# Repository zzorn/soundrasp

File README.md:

soundrasp
=========

Modular sound synthetizator, with designs for a physical controller.

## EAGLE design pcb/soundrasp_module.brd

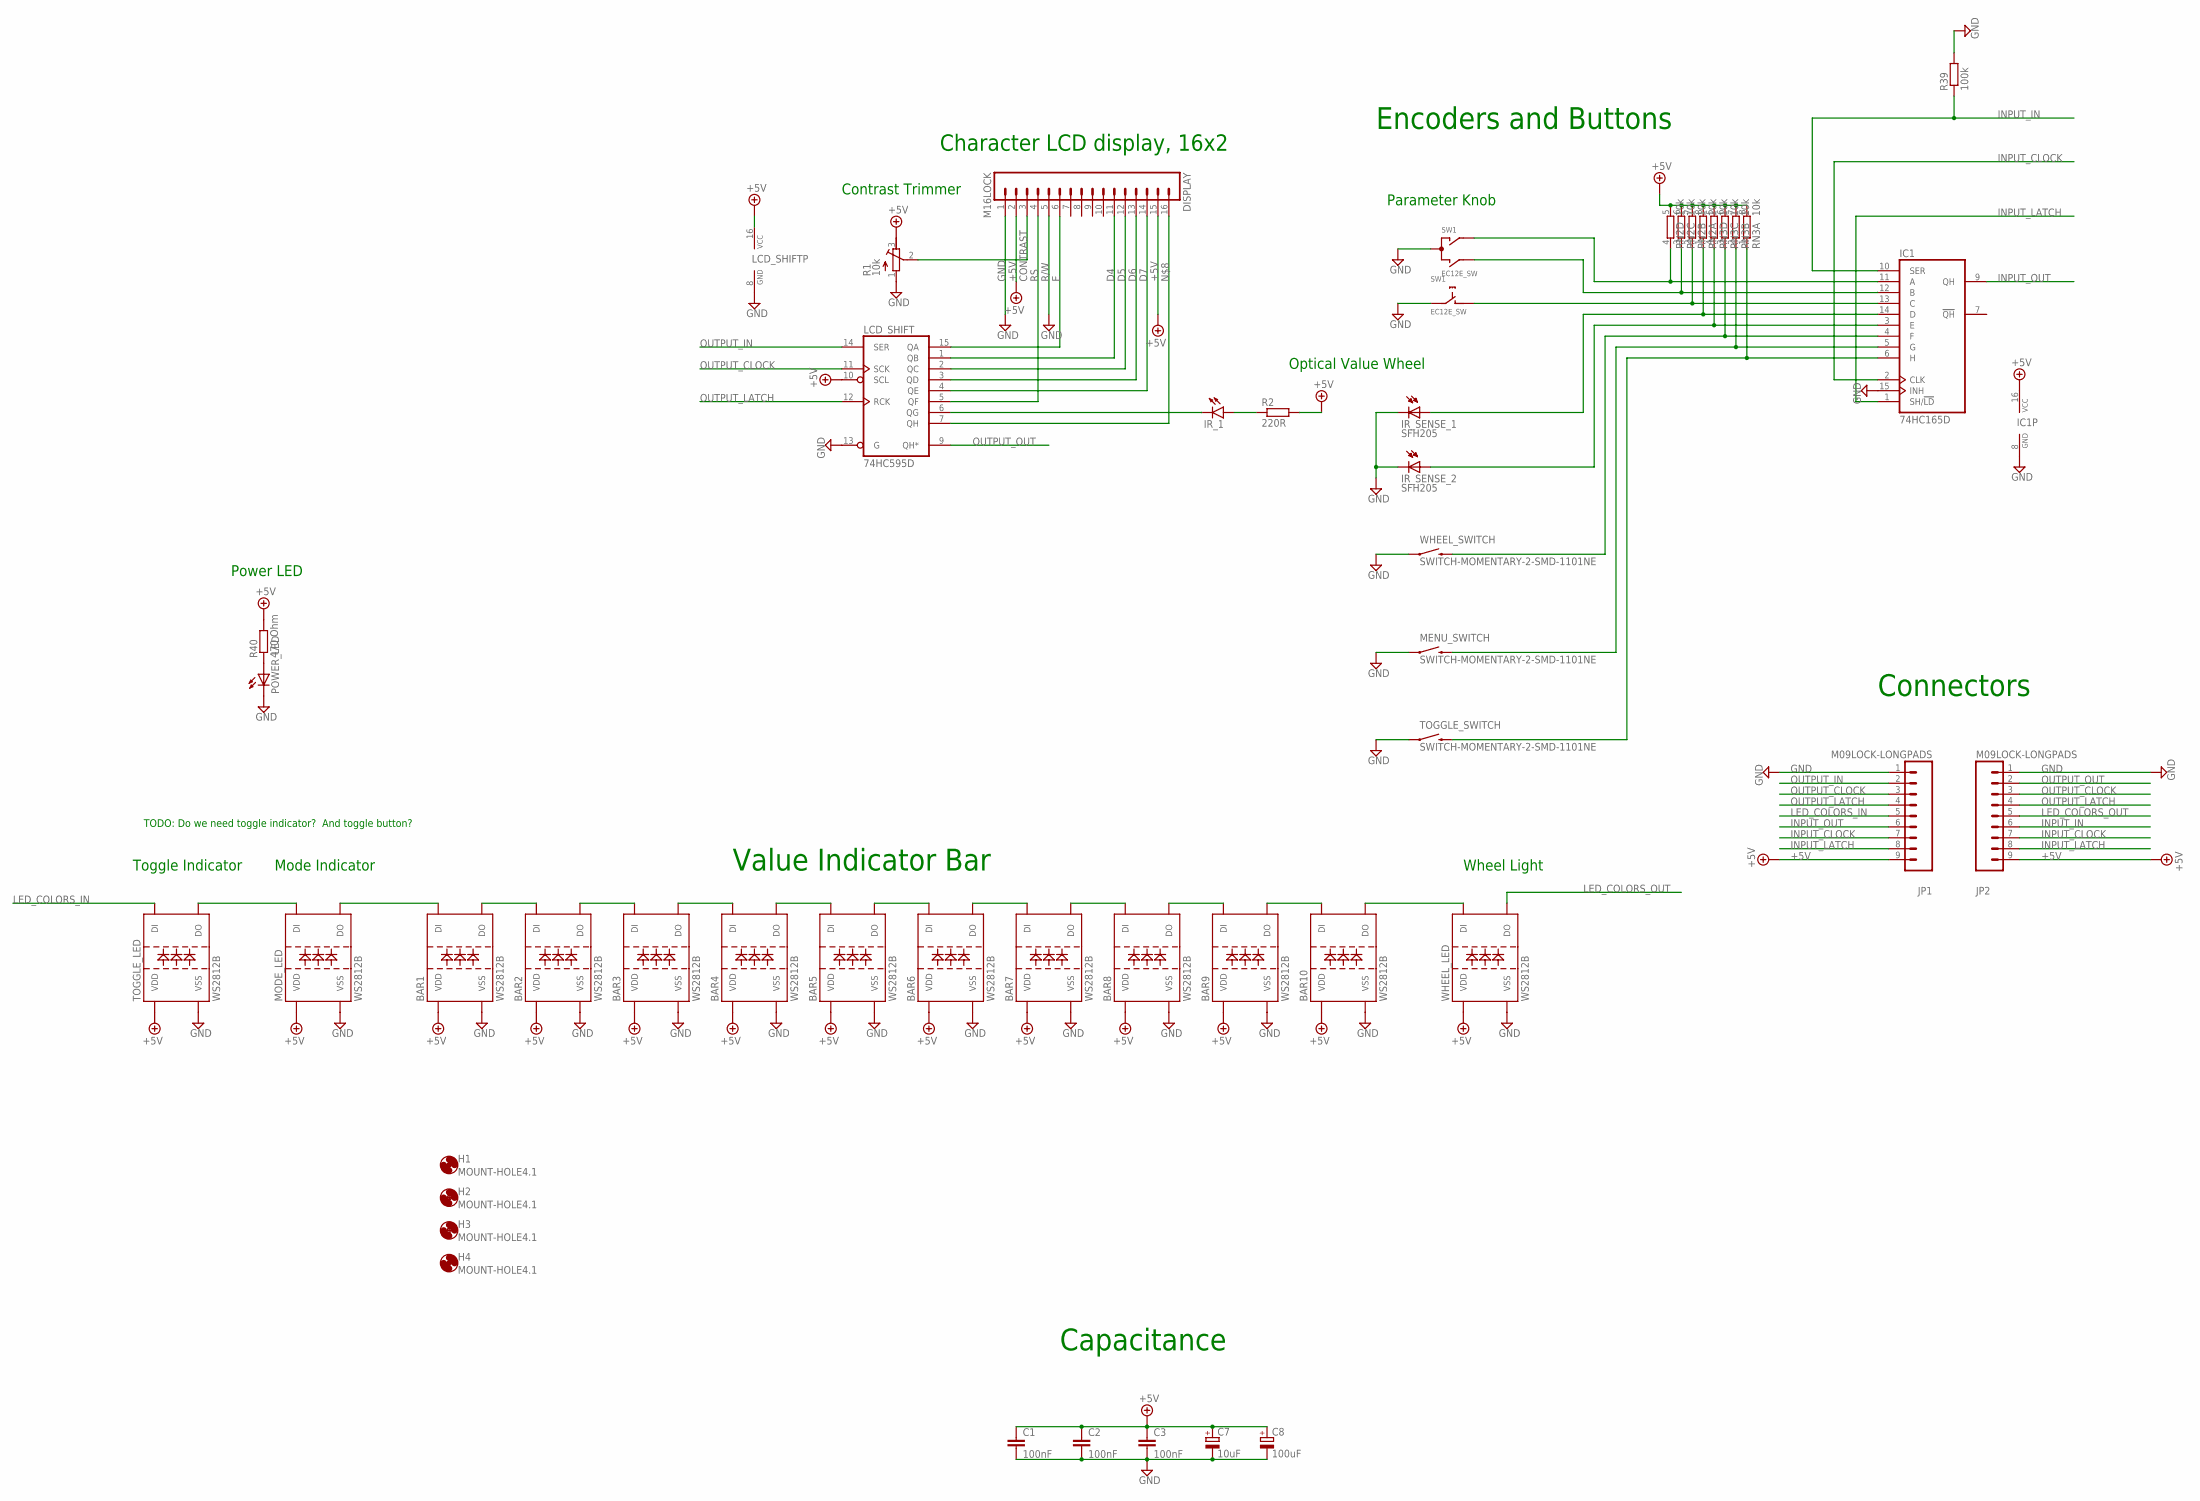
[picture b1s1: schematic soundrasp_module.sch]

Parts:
BAR1, BAR2, BAR3, BAR4, BAR5, BAR6, BAR7, BAR8, BAR9, BAR10: WS2812B
C1, C2, C3: 100nF; C0805
C7: 10uF; E2,5-7
C8: 100uF; E2,5-7
DISPLAY: M16LOCK; 1X16_LOCK
H1, H2, H3, H4: MOUNT-HOLE4.1; 4,1
IC1: 74HC165D; SO16
IR_1: LED3MM
IR_SENSE_1, IR_SENSE_2: SFH205
JP1, JP2: M09LOCK-LONGPADS; 1X09_LOCK_LONGPADS
LCD_SHIFT: 74HC595D; SO16
MENU_SWITCH: SWITCH-MOMENTARY-2-SMD-1101NE; TACTILE-SWITCH-1101NE
MODE_LED: WS2812B
POWER_LED: LEDCHIPLED_0805; CHIPLED_0805
R1: 10k; RTRIM3296W
R2: 220R; R0805
R39: 100k; R0805
R40: 470 Ohm; R0805
RN2, RN3: 10k; 0603-ARV
SW1: EC12E_SW; ALPS_EC12E_SW
TOGGLE_LED: WS2812B
TOGGLE_SWITCH: SWITCH-MOMENTARY-2-SMD-1101NE; TACTILE-SWITCH-1101NE
WHEEL_LED: WS2812B
WHEEL_SWITCH: SWITCH-MOMENTARY-2-SMD-1101NE; TACTILE-SWITCH-1101NE

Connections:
+5V: BAR1.1 (VDD), BAR2.1 (VDD), BAR3.1 (VDD), BAR4.1 (VDD), BAR5.1 (VDD), BAR6.1 (VDD), BAR7.1 (VDD), BAR8.1 (VDD), BAR9.1 (VDD), BAR10.1 (VDD), C1.1, C2.1, C3.1, C7.+, C8.+, DISPLAY.2, DISPLAY.15, IC1.16 (VCC), JP1.9, JP2.9, LCD_SHIFT.10 (SCL), LCD_SHIFT.16 (VCC), MODE_LED.1 (VDD), R1.3 (E), R2.2, R40.2, RN2.5 (2), RN2.6 (2), RN2.7 (2), RN2.8 (2), RN3.5 (2), RN3.6 (2), RN3.7 (2), RN3.8 (2), TOGGLE_LED.1 (VDD), WHEEL_LED.1 (VDD)
BAR7: BAR6.2 (DO), BAR7.4 (DI)
CONTRAST: DISPLAY.3, R1.2 (S)
D4: DISPLAY.11, LCD_SHIFT.1 (QB)
D5: DISPLAY.12, LCD_SHIFT.2 (QC)
D6: DISPLAY.13, LCD_SHIFT.3 (QD)
D7: DISPLAY.14, LCD_SHIFT.4 (QE)
E: DISPLAY.6, LCD_SHIFT.15 (QA)
GND: BAR1.3 (VSS), BAR2.3 (VSS), BAR3.3 (VSS), BAR4.3 (VSS), BAR5.3 (VSS), BAR6.3 (VSS), BAR7.3 (VSS), BAR8.3 (VSS), BAR9.3 (VSS), BAR10.3 (VSS), C1.2, C2.2, C3.2, C7.-, C8.-, DISPLAY.1, IC1.8 (GND), IC1.15 (INH), IR_SENSE_1.K (C), IR_SENSE_2.K (C), JP1.1, JP2.1, LCD_SHIFT.8 (GND), LCD_SHIFT.13 (G), MENU_SWITCH.P$1 (1), MODE_LED.3 (VSS), POWER_LED.C, R1.1 (A), R39.2, SW1.C, SW1.E (2), TOGGLE_LED.3 (VSS), TOGGLE_SWITCH.P$1 (1), WHEEL_LED.3 (VSS), WHEEL_SWITCH.P$1 (1)
INPUT_CLOCK: IC1.2 (CLK), JP1.7, JP2.7
INPUT_IN: IC1.10 (SER), JP2.6, R39.1
INPUT_LATCH: IC1.1 (SH/!LD), JP1.8, JP2.8
INPUT_OUT: IC1.9 (QH), JP1.6
LED_COLORS_IN: JP1.5, TOGGLE_LED.4 (DI)
LED_COLORS_OUT: JP2.5, WHEEL_LED.2 (DO)
unnamed: IR_1.A, R2.1
unnamed: IC1.11 (A), RN2.4 (1), SW1.A
unnamed: IC1.12 (B), RN2.3 (1), SW1.B
unnamed: IC1.14 (D), IR_SENSE_1.A, RN2.1
unnamed: IC1.3 (E), IR_SENSE_2.A, RN3.4 (1)
unnamed: IC1.13 (C), RN2.2 (1), SW1.D (1)
unnamed: IC1.4 (F), RN3.3 (1), WHEEL_SWITCH.P$2 (2)
unnamed: DISPLAY.16, LCD_SHIFT.7 (QH)
unnamed: BAR8.2 (DO), BAR9.4 (DI)
unnamed: BAR9.2 (DO), BAR10.4 (DI)
unnamed: BAR10.2 (DO), WHEEL_LED.4 (DI)
unnamed: MODE_LED.4 (DI), TOGGLE_LED.2 (DO)
unnamed: BAR1.4 (DI), MODE_LED.2 (DO)
unnamed: IR_1.K (C), LCD_SHIFT.6 (QG)
unnamed: BAR1.2 (DO), BAR2.4 (DI)
unnamed: BAR2.2 (DO), BAR3.4 (DI)
unnamed: BAR3.2 (DO), BAR4.4 (DI)
unnamed: BAR4.2 (DO), BAR5.4 (DI)
unnamed: BAR5.2 (DO), BAR6.4 (DI)
unnamed: BAR7.2 (DO), BAR8.4 (DI)
unnamed: IC1.5 (G), MENU_SWITCH.P$2 (2), RN3.2 (1)
unnamed: POWER_LED.A, R40.1
unnamed: IC1.6 (H), RN3.1, TOGGLE_SWITCH.P$2 (2)
OUTPUT_CLOCK: JP1.3, JP2.3, LCD_SHIFT.11 (SCK)
OUTPUT_IN: JP1.2, LCD_SHIFT.14 (SER)
OUTPUT_LATCH: JP1.4, JP2.4, LCD_SHIFT.12 (RCK)
OUTPUT_OUT: JP2.2, LCD_SHIFT.9 (QH*)
R/W: DISPLAY.5
RS: DISPLAY.4, LCD_SHIFT.5 (QF)

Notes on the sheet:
Connectors
Value Indicator Bar
Capacitance
Encoders and Buttons
Wheel Light
Contrast Trimmer
Power LED
Optical Value Wheel
Parameter Knob
Mode Indicator
Character LCD display, 16x2
Toggle Indicator
TODO: Do we need toggle indicator? And toggle button?

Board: 2 copper layers, 41 parts (2 on the bottom side), 43 nets, no tracks yet.

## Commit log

2012-12-09 Updated gitignore.
2012-12-09 Ignore unneeded project files.
2012-12-09 Ignore compiled binaries.
2012-12-09 Updated readme.
2012-12-09 Initial source files.
2012-12-09 Code blocks project file.
2012-12-09 Changed to use printf consistently, instead of mixing in iostream.
2012-12-11 Work on modules, getting some noise out, but weird increasing pitch bug.
2012-12-11 Multiply phase with Tau so that we get 1 phase = 1 wavelength.
2012-12-11 Split the code into separate files for greater clarity.
2012-12-11 Started working on display, added two debug displays.
2012-12-13 Fixed phase issue.
2012-12-13 Adjusting scaling.
2012-12-19 Showing all modules.
2013-03-15 Moved C++ sources to subdir.
2013-03-15 Working on libgdx version
2013-08-29 Created PCB for a soundrasp control module.
2013-08-30 More work on soundrasp pcb.
2013-08-31 More work on pcb.
2013-09-03 Work on soundrasp pcb.
2013-10-10 Work on soundrasp module pcb.
2013-10-10 Started working on 3D model.
2014-05-21 Switched to Eagle 6+ version. Switched to addressable WS2812B LEDs.
2014-05-22 Refactoring scema and doing initial pcb layout.
2014-05-23 Moved old java and cpp code to separate directory.
2014-05-23 Worked on code, basic sound output works.
2014-05-24 Refactored the Synth class, extracted AudioOutput to handle actual audio playing. Created model classes for the Patch and Slots. Tuned buffering to a minimum.
2014-05-24 Implemented parameters. Added ModuleType and a repository for ModuleTypes.
2014-05-25 Tuned tests
2014-05-26 Added a number of new modules. Changed playback to work through an OutputModule .
2014-05-29 Specified java version.
2014-06-10 Implemented initial crude UI
2014-06-17 Updated module to new case structure. Removed redundant display PCB.
2014-06-18 Removed force feedback. Changed design to use one common IR LED.
2014-07-01 Tuned schema and board.
2014-07-15 Made LCD backlight controllable.
2014-11-07 Refactored and simplified SoundRasp by removing the slot concept, and making patches composite modules.

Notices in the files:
parts and their libraries:
SparkFun-Connectors: Licensing: Creative Commons ShareAlike 4.0 International - https://creativecommons.org/licenses/by-sa/4.0
